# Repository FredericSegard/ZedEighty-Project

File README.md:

# ZedEighty Project
 My Z80 adventures

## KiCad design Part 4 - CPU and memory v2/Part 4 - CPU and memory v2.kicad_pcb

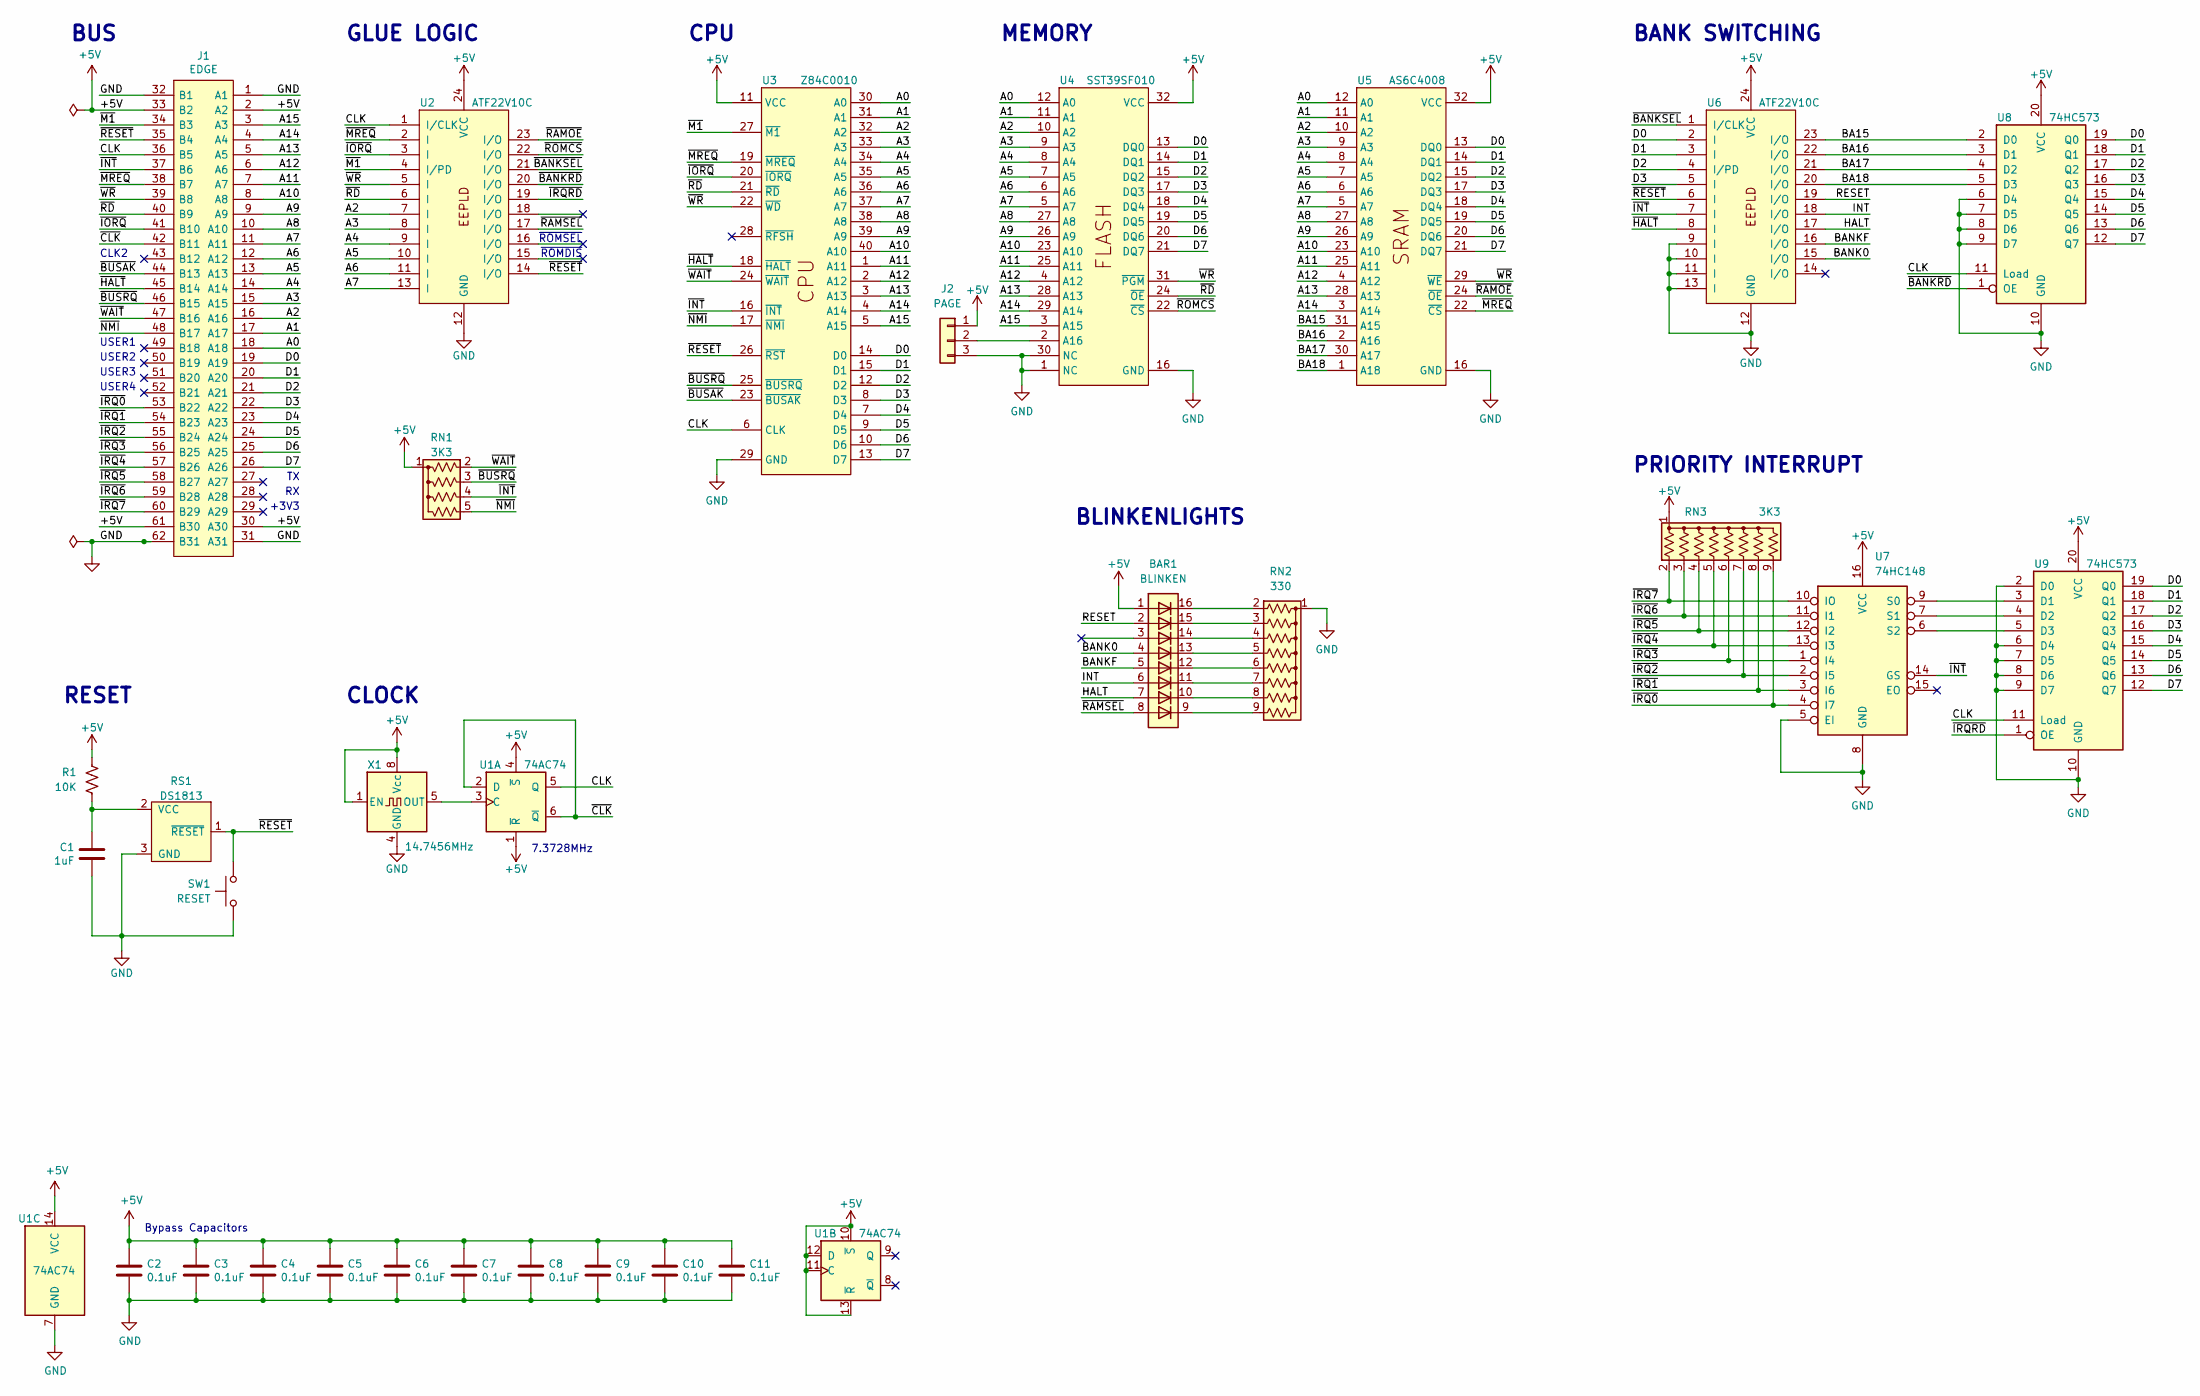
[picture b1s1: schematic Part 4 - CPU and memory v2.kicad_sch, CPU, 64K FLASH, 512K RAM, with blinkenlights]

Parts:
BAR1: BLINKEN; 8_Segment_Bar_graph
C1: 1uF; C_Disc_D3.0mm_W2.0mm_P2.50mm
C2, C3, C4, C5, C6, C7, C8, C9, C10, C11: 0.1uF; C_Disc_D3.0mm_W1.6mm_P2.50mm
J1: EDGE; BUS_XT; Mouser Part Number 571-6-5530843-5
J2: PAGE; PinHeader_1x03_P2.54mm_Vertical
R1: 10K; R_Axial_DIN0207_L6.3mm_D2.5mm_P10.16mm_Horizontal
RN1: 3K3; R_Array_SIP5
RN2: 330; R_Array_SIP9
RN3: 3K3; R_Array_SIP9
RS1: DS1813; TO-92L_Inline_Wide
SW1: RESET; SW_Tactile_SPST_Angled_PTS645Vx58-2LFS
U1: 74AC74; DIP-14_W7.62mm_Socket
U2, U6: ATF22V10C; DIP-24_W7.62mm_Socket
U3: Z84C0010; DIP-40_W15.24mm_Socket
U4: SST39SF010; DIP_Socket-32_W11.9_W12.7_W15.24_W17.78_W18.5_3M_232-1285-0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
U5: AS6C4008; DIP-32_W15.24mm_Socket
U7: 74HC148; DIP-16_W7.62mm_Socket
U8, U9: 74HC573; DIP-20_W7.62mm_Socket
X1: 14.7456MHz; DIP-8-4_W7.62mm_Oscillator_Socket

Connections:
+5V: BAR1.1 (A), C2.1, C3.1, C4.1, C5.1, C6.1, C7.1, C8.1, C9.1, C10.1, C11.1, J1.2 (A2), J1.30 (A30), J1.33 (B2), J1.61 (B30), J2.1, R1.2, RN1.1 (common), RN3.1 (common), U1.1 (~R), U1.4 (~S), U1.10 (~S), U1.11 (C), U1.12 (D), U1.13 (~R), U1.14 (VCC), U2.24 (VCC), U3.11 (VCC), U4.32 (VCC), U5.32 (VCC), U6.24 (VCC), U7.16 (VCC), U8.20 (VCC), U9.20 (VCC), X1.1 (EN), X1.8 (Vcc)
/A0: J1.18 (A18), U3.30 (A0), U4.12 (A0), U5.12 (A0)
/A1: J1.17 (A17), U3.31 (A1), U4.11 (A1), U5.11 (A1)
/A2: J1.16 (A16), U2.7 (I), U3.32 (A2), U4.10 (A2), U5.10 (A2)
/A3: J1.15 (A15), U2.8 (I), U3.33 (A3), U4.9 (A3), U5.9 (A3)
/A4: J1.14 (A14), U2.9 (I), U3.34 (A4), U4.8 (A4), U5.8 (A4)
/A5: J1.13 (A13), U2.10 (I), U3.35 (A5), U4.7 (A5), U5.7 (A5)
/A6: J1.12 (A12), U2.11 (I), U3.36 (A6), U4.6 (A6), U5.6 (A6)
/A7: J1.11 (A11), U2.13 (I), U3.37 (A7), U4.5 (A7), U5.5 (A7)
/A8: J1.10 (A10), U3.38 (A8), U4.27 (A8), U5.27 (A8)
/A9: J1.9 (A9), U3.39 (A9), U4.26 (A9), U5.26 (A9)
/A10: J1.8 (A8), U3.40 (A10), U4.23 (A10), U5.23 (A10)
/A11: J1.7 (A7), U3.1 (A11), U4.25 (A11), U5.25 (A11)
/A12: J1.6 (A6), U3.2 (A12), U4.4 (A12), U5.4 (A12)
/A13: J1.5 (A5), U3.3 (A13), U4.28 (A13), U5.28 (A13)
/A14: J1.4 (A4), U3.4 (A14), U4.29 (A14), U5.3 (A14)
/A15: J1.3 (A3), U3.5 (A15), U4.3 (A15)
/BA15: U5.31 (A15), U6.23 (I/O), U8.2 (D0)
/BA16: U5.2 (A16), U6.22 (I/O), U8.3 (D1)
/BA17: U5.30 (A17), U6.21 (I/O), U8.4 (D2)
/BA18: U5.1 (A18), U6.20 (I/O), U8.5 (D3)
/BANK0: BAR1.4 (A), U6.15 (I/O)
/BANKF: BAR1.5 (A), U6.16 (I/O)
/CLK: J1.36 (B5), U1.5 (Q), U2.1 (I/CLK), U3.6 (CLK), U8.11 (Load), U9.11 (Load)
/D0: J1.19 (A19), U3.14 (D0), U4.13 (DQ0), U5.13 (DQ0), U6.2 (I), U8.19 (Q0), U9.19 (Q0)
/D1: J1.20 (A20), U3.15 (D1), U4.14 (DQ1), U5.14 (DQ1), U6.3 (I), U8.18 (Q1), U9.18 (Q1)
/D2: J1.21 (A21), U3.12 (D2), U4.15 (DQ2), U5.15 (DQ2), U6.4 (I/PD), U8.17 (Q2), U9.17 (Q2)
/D3: J1.22 (A22), U3.8 (D3), U4.17 (DQ3), U5.17 (DQ3), U6.5 (I), U8.16 (Q3), U9.16 (Q3)
/D4: J1.23 (A23), U3.7 (D4), U4.18 (DQ4), U5.18 (DQ4), U8.15 (Q4), U9.15 (Q4)
/D5: J1.24 (A24), U3.9 (D5), U4.19 (DQ5), U5.19 (DQ5), U8.14 (Q5), U9.14 (Q5)
/D6: J1.25 (A25), U3.10 (D6), U4.20 (DQ6), U5.20 (DQ6), U8.13 (Q6), U9.13 (Q6)
/D7: J1.26 (A26), U3.13 (D7), U4.21 (DQ7), U5.21 (DQ7), U8.12 (Q7), U9.12 (Q7)
/HALT: BAR1.7 (A), U6.17 (I/O)
/INT: BAR1.6 (A), U6.18 (I/O)
/RESET: BAR1.2 (A), U6.19 (I/O)
/~BANKRD: U2.20 (I/O), U8.1 (OE)
/~BANKSEL: U2.21 (I/O), U6.1 (I/CLK)
/~BUSAK: J1.44 (B13), U3.23 (~BUSAK)
/~BUSRQ: J1.46 (B15), RN1.3 (R2), U3.25 (~BUSRQ)
/~CLK: J1.42 (B11), U1.2 (D), U1.6 (~Q)
/~HALT: J1.45 (B14), U3.18 (~HALT), U6.8 (I)
/~INT: J1.37 (B6), RN1.4 (R3), U3.16 (~INT), U6.7 (I), U7.14 (GS)
/~IORQ: J1.41 (B10), U2.3 (I), U3.20 (~IORQ)
/~IRQ0: J1.53 (B22), RN3.9 (R8), U7.4 (I7)
/~IRQ1: J1.54 (B23), RN3.8 (R7), U7.3 (I6)
/~IRQ2: J1.55 (B24), RN3.7 (R6), U7.2 (I5)
/~IRQ3: J1.56 (B25), RN3.6 (R5), U7.1 (I4)
/~IRQ4: J1.57 (B26), RN3.5 (R4), U7.13 (I3)
/~IRQ5: J1.58 (B27), RN3.4 (R3), U7.12 (I2)
/~IRQ6: J1.59 (B28), RN3.3 (R2), U7.11 (I1)
/~IRQ7: J1.60 (B29), RN3.2 (R1), U7.10 (IO)
/~IRQRD: U2.19 (I/O), U9.1 (OE)
/~M1: J1.34 (B3), U2.4 (I/PD), U3.27 (~M1)
/~MREQ: J1.38 (B7), U2.2 (I), U3.19 (~MREQ), U5.22 (~CS)
/~NMI: J1.48 (B17), RN1.5 (R4), U3.17 (~NMI)
/~RAMOE: U2.23 (I/O), U5.24 (~OE)
/~RAMSEL: BAR1.8 (A), U2.17 (I/O)
/~RD: J1.40 (B9), U2.6 (I), U3.21 (~RD), U4.24 (~OE)
/~RESET: J1.35 (B4), RS1.1 (~RESET), SW1.1, U2.14 (I/O), U3.26 (~RST), U6.6 (I)
/~ROMCS: U2.22 (I/O), U4.22 (~CS)
/~WAIT: J1.47 (B16), RN1.2 (R1), U3.24 (~WAIT)
/~WR: J1.39 (B8), U2.5 (I), U3.22 (~WD), U4.31 (~PGM), U5.29 (~WE)
GND: C1.2, C2.2, C3.2, C4.2, C5.2, C6.2, C7.2, C8.2, C9.2, C10.2, C11.2, J1.1 (A1), J1.31 (A31), J1.32 (B1), J1.62 (B31), J2.3, RN2.1 (common), RS1.3 (GND), SW1.2, U1.7 (GND), U2.12 (GND), U3.29 (GND), U4.1 (NC), U4.16 (GND), U4.30 (NC), U5.16 (GND), U6.9 (I), U6.10 (I), U6.11 (I), U6.12 (GND), U6.13 (I), U7.5 (EI), U7.8 (GND), U8.6 (D4), U8.7 (D5), U8.8 (D6), U8.9 (D7), U8.10 (GND), U9.2 (D0), U9.6 (D4), U9.7 (D5), U9.8 (D6), U9.9 (D7), U9.10 (GND), X1.4 (GND)
unnamed: BAR1.9 (A), RN2.9 (R8)
unnamed: BAR1.10 (A), RN2.8 (R7)
unnamed: BAR1.11 (K), RN2.7 (R6)
unnamed: BAR1.12 (K), RN2.6 (R5)
unnamed: BAR1.13 (K), RN2.5 (R4)
unnamed: BAR1.14 (K), RN2.4 (R3)
unnamed: BAR1.15 (K), RN2.3 (R2)
unnamed: BAR1.16 (K), RN2.2 (R1)
unnamed: C1.1, R1.1, RS1.2 (VCC)
unnamed: J2.2, U4.2 (A16)
unnamed: U1.3 (C), X1.5 (OUT)
unnamed: U7.6 (S2), U9.5 (D3)
unnamed: U7.7 (S1), U9.4 (D2)
unnamed: U7.9 (S0), U9.3 (D1)

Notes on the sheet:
MEMORY
BUS
BLINKENLIGHTS
CLK2
CPU
PRIORITY INTERRUPT
USER2
RESET
USER4
7.3728MHz
BANK SWITCHING
USER3
USER1
~{ROMDIS}
Bypass Capacitors
CLOCK
GLUE LOGIC
+3V3
~{ROMSEL}

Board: 2 copper layers, 30 parts (0 on the bottom side), 77 nets, no tracks yet.

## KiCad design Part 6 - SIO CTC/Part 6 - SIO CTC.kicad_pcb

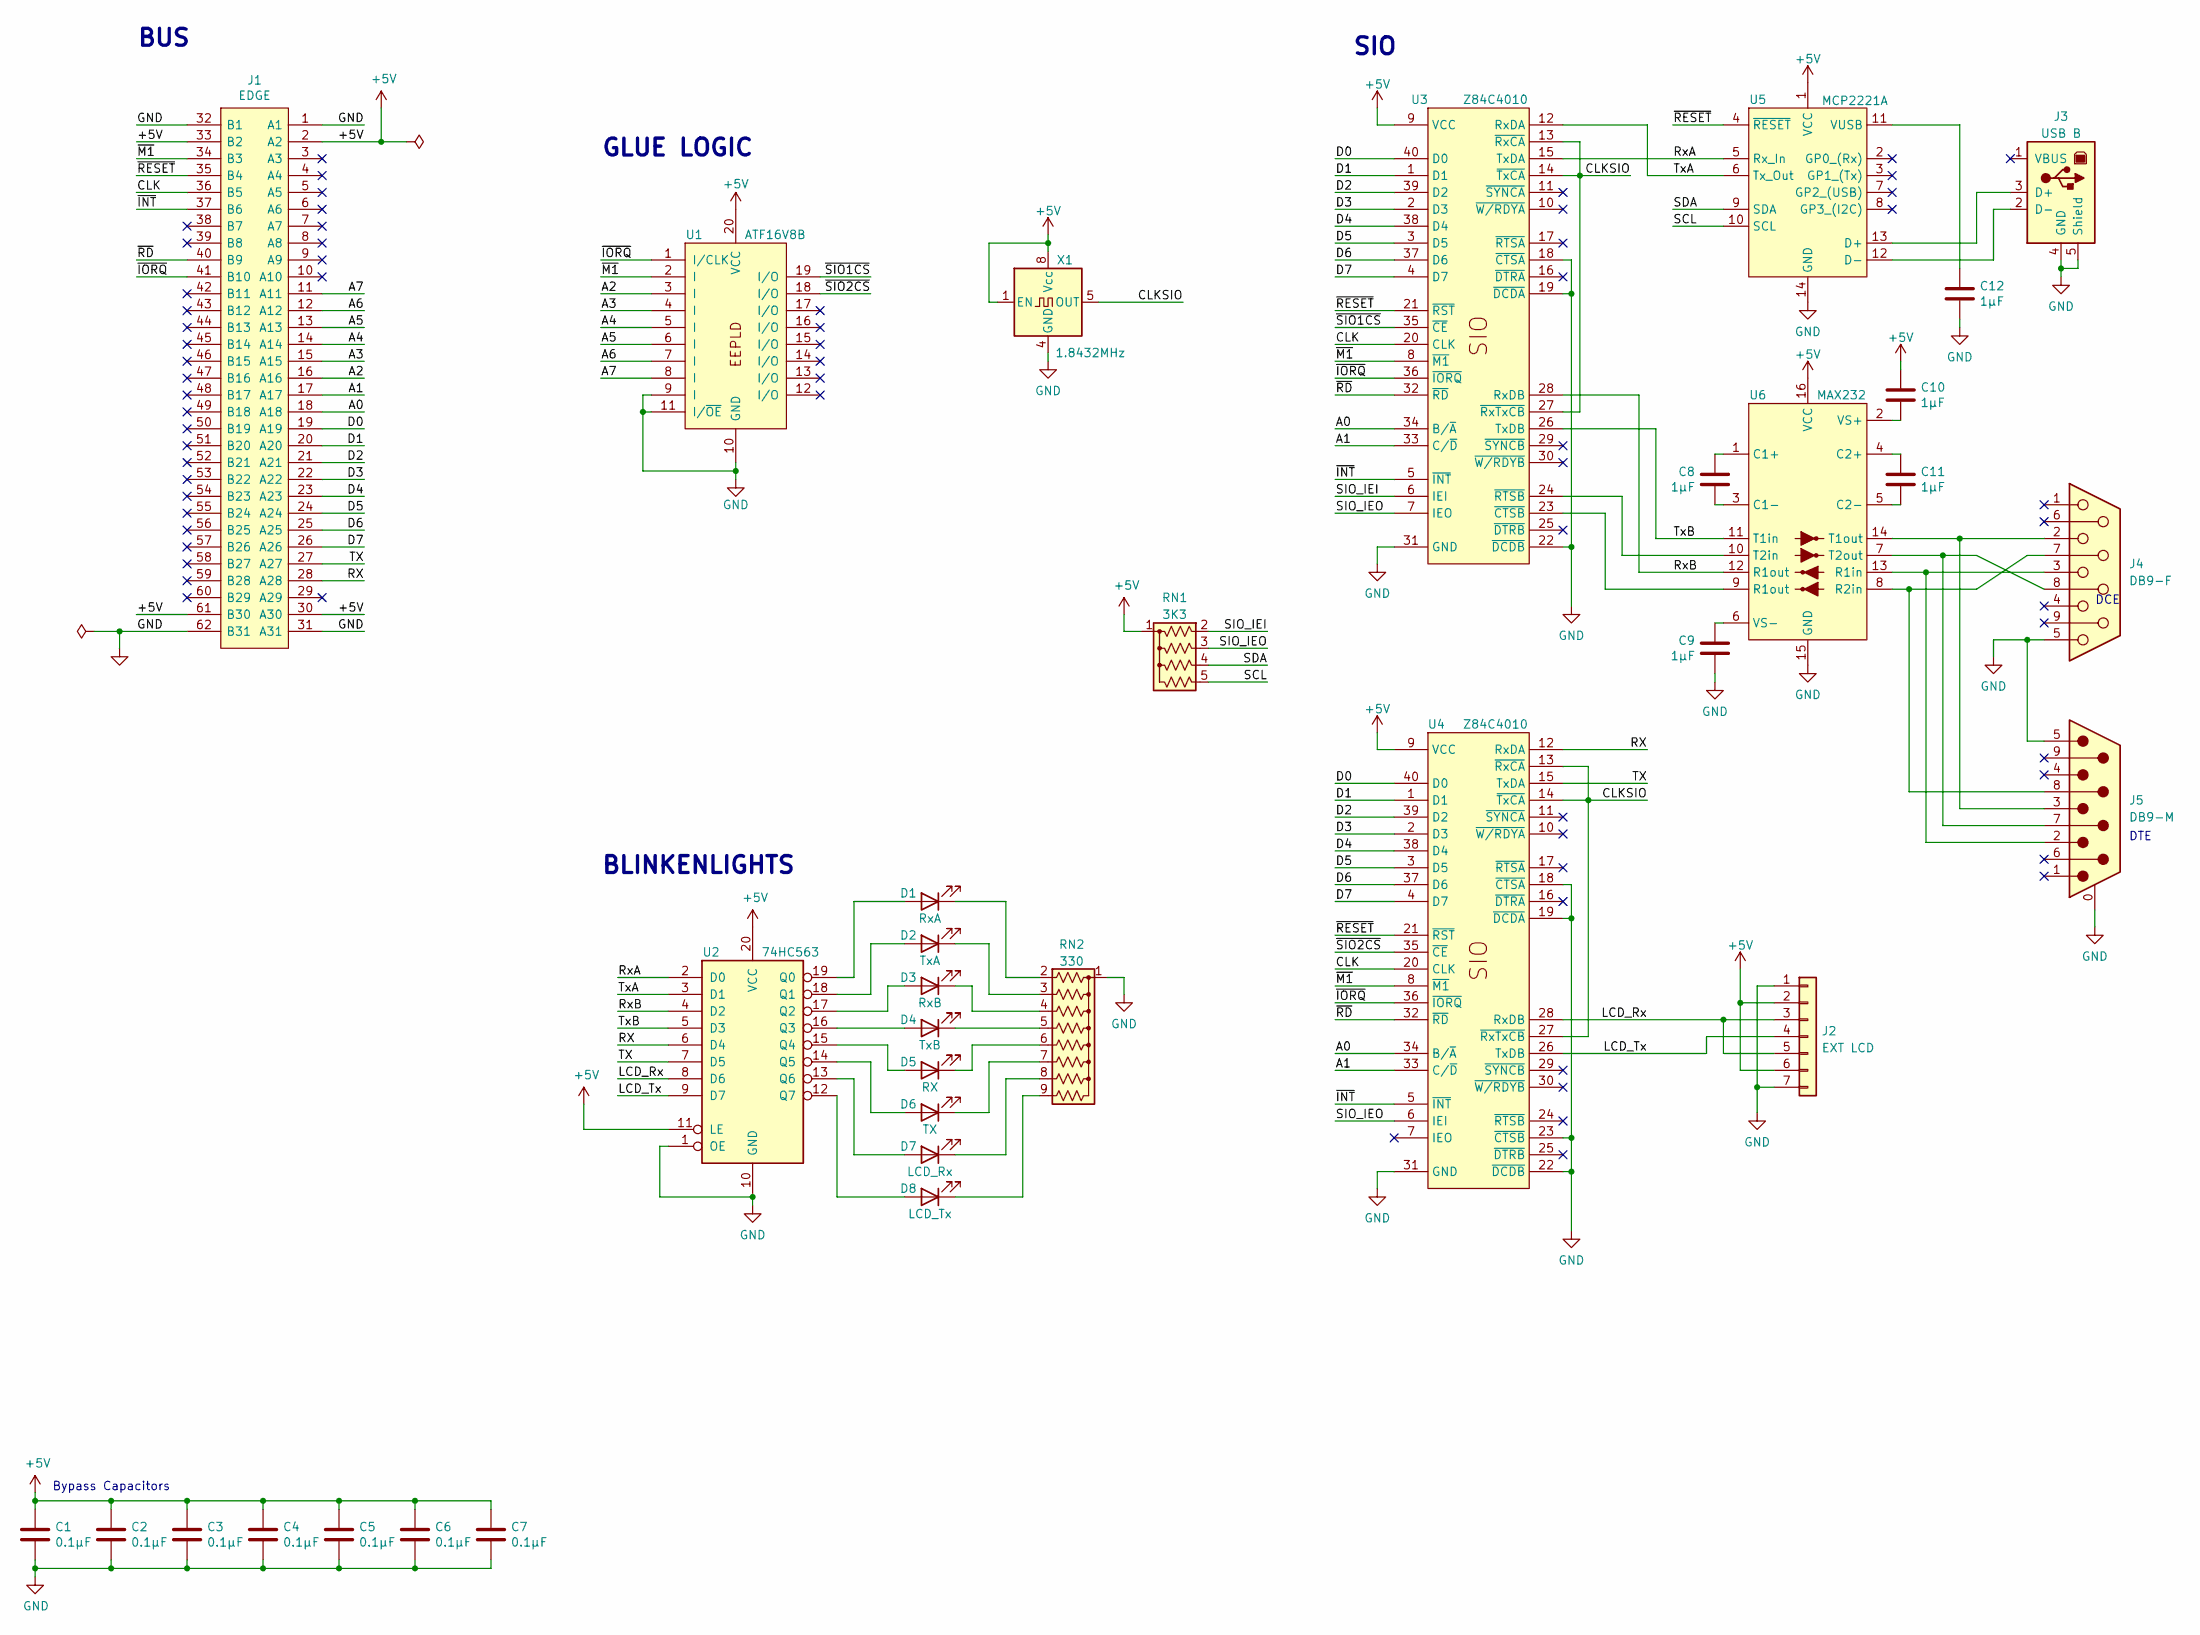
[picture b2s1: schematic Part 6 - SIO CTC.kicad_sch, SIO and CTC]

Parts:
C1, C2, C3, C4, C5, C6, C7: 0.1µF; C_Disc_D3.0mm_W1.6mm_P2.50mm
C8, C9, C10, C11, C12: 1µF; C_Disc_D3.0mm_W1.6mm_P2.50mm
D1: RxA; LED_D3.0mm_Horizontal_O1.27mm_Z2.0mm_Clear
D2: TxA; LED_D3.0mm_Horizontal_O1.27mm_Z2.0mm_Clear
D3: RxB; LED_D3.0mm_Horizontal_O1.27mm_Z2.0mm_Clear
D4: TxB; LED_D3.0mm_Horizontal_O1.27mm_Z2.0mm_Clear
D5: RX; LED_D3.0mm_Horizontal_O1.27mm_Z2.0mm_Clear
D6: TX; LED_D3.0mm_Horizontal_O1.27mm_Z2.0mm_Clear
D7: LCD_Rx; LED_D3.0mm_Horizontal_O1.27mm_Z2.0mm_Clear
D8: LCD_Tx; LED_D3.0mm_Horizontal_O1.27mm_Z2.0mm_Clear
J1: EDGE; BUS_XT; Mouser Part Number 571-6-5530843-5
J2: EXT LCD; PinHeader_1x07_P2.54mm_Horizontal
J3: USB B; USB_B_Lumberg_2411_02_Horizontal
J4: DB9-F; DSUB-9_Female_Horizontal_P2.77x2.84mm_EdgePinOffset7.70mm_H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
J5: DB9-M; DSUB-9_Male_Horizontal_P2.77x2.84mm_EdgePinOffset7.70mm_Hou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
RN1: 3K3; R_Array_SIP5
RN2: 330; R_Array_SIP9
U1: ATF16V8B; DIP-20_W7.62mm_Socket
U2: 74HC563; DIP-20_W7.62mm_Socket
U3, U4: Z84C4010; DIP-40_W15.24mm_Socket
U5: MCP2221A; DIP-14_W7.62mm_Socket
U6: MAX232; DIP-16_W7.62mm_Socket
X1: 1.8432MHz; DIP-8-4_W7.62mm_Oscillator_Socket

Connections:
+5V: C1.1, C2.1, C3.1, C4.1, C5.1, C6.1, C7.1, C10.1, J1.2 (A2), J1.30 (A30), J1.33 (B2), J1.61 (B30), J2.2, J2.6, RN1.1 (common), U1.20 (VCC), U2.11 (LE), U2.20 (VCC), U3.9 (VCC), U4.9 (VCC), U5.1 (VCC), U6.16 (VCC), X1.1 (EN), X1.8 (Vcc)
/A0: J1.18 (A18), U3.34 (B/~A), U4.34 (B/~A)
/A1: J1.17 (A17), U3.33 (C/~D), U4.33 (C/~D)
/A2: J1.16 (A16), U1.3 (I)
/A3: J1.15 (A15), U1.4 (I)
/A4: J1.14 (A14), U1.5 (I)
/A5: J1.13 (A13), U1.6 (I)
/A6: J1.12 (A12), U1.7 (I)
/A7: J1.11 (A11), U1.8 (I)
/CLK: J1.36 (B5), U3.20 (CLK), U4.20 (CLK)
/CLKSIO: U3.13 (~RxCA), U3.14 (~TxCA), U3.27 (~RxTxCB), U4.13 (~RxCA), U4.14 (~TxCA), U4.27 (~RxTxCB), X1.5 (OUT)
/D0: J1.19 (A19), U3.40 (D0), U4.40 (D0)
/D1: J1.20 (A20), U3.1 (D1), U4.1 (D1)
/D2: J1.21 (A21), U3.39 (D2), U4.39 (D2)
/D3: J1.22 (A22), U3.2 (D3), U4.2 (D3)
/D4: J1.23 (A23), U3.38 (D4), U4.38 (D4)
/D5: J1.24 (A24), U3.3 (D5), U4.3 (D5)
/D6: J1.25 (A25), U3.37 (D6), U4.37 (D6)
/D7: J1.26 (A26), U3.4 (D7), U4.4 (D7)
/LCD_Rx: J2.3, J2.5, U2.8 (D6), U4.28 (RxDB)
/LCD_Tx: J2.4, U2.9 (D7), U4.26 (TxDB)
/RX: J1.28 (A28), U2.6 (D4), U4.12 (RxDA)
/RxA: U2.2 (D0), U3.15 (TxDA), U5.5 (Rx_In)
/RxB: U2.4 (D2), U3.28 (RxDB), U6.12 (R1out)
/SCL: RN1.5 (R4), U5.10 (SCL)
/SDA: RN1.4 (R3), U5.9 (SDA)
/SIO_IEI: RN1.2 (R1), U3.6 (IEI)
/SIO_IEO: RN1.3 (R2), U3.7 (IEO), U4.6 (IEI)
/TX: J1.27 (A27), U2.7 (D5), U4.15 (TxDA)
/TxA: U2.3 (D1), U3.12 (RxDA), U5.6 (Tx_Out)
/TxB: U2.5 (D3), U3.26 (TxDB), U6.11 (T1in)
/~INT: J1.37 (B6), U3.5 (~INT), U4.5 (~INT)
/~IORQ: J1.41 (B10), U1.1 (I/CLK), U3.36 (~IORQ), U4.36 (~IORQ)
/~M1: J1.34 (B3), U1.2 (I), U3.8 (~M1), U4.8 (~M1)
/~RD: J1.40 (B9), U3.32 (~RD), U4.32 (~RD)
/~RESET: J1.35 (B4), U3.21 (~RST), U4.21 (~RST), U5.4 (~RESET)
/~SIO1CS: U1.19 (I/O), U3.35 (~CE)
/~SIO2CS: U1.18 (I/O), U4.35 (~CE)
GND: C1.2, C2.2, C3.2, C4.2, C5.2, C6.2, C7.2, C9.2, C12.2, J1.1 (A1), J1.31 (A31), J1.32 (B1), J1.62 (B31), J2.1, J2.7, J3.4 (GND), J3.5 (Shield), J4.5, J5.0 (PAD), J5.5, RN2.1 (common), U1.9 (I), U1.10 (GND), U1.11 (I/~OE), U2.1 (OE), U2.10 (GND), U3.18 (~CTSA), U3.19 (~DCDA), U3.22 (~DCDB), U3.31 (GND), U4.18 (~CTSA), U4.19 (~DCDA), U4.22 (~DCDB), U4.23 (~CTSB), U4.31 (GND), U5.14 (GND), U6.15 (GND), X1.4 (GND)
unnamed: C8.1, U6.1 (C1+)
unnamed: C8.2, U6.3 (C1-)
unnamed: C9.1, U6.6 (VS-)
unnamed: C10.2, U6.2 (VS+)
unnamed: C11.1, U6.4 (C2+)
unnamed: C11.2, U6.5 (C2-)
unnamed: C12.1, U5.11 (VUSB)
unnamed: D1.1 (K), RN2.2 (R1)
unnamed: D1.2 (A), U2.19 (Q0)
unnamed: D2.1 (K), RN2.3 (R2)
unnamed: D2.2 (A), U2.18 (Q1)
unnamed: D3.1 (K), RN2.4 (R3)
unnamed: D3.2 (A), U2.17 (Q2)
unnamed: D4.1 (K), RN2.5 (R4)
unnamed: D4.2 (A), U2.16 (Q3)
unnamed: D5.1 (K), RN2.6 (R5)
unnamed: D5.2 (A), U2.15 (Q4)
unnamed: D6.1 (K), RN2.7 (R6)
unnamed: D6.2 (A), U2.14 (Q5)
unnamed: D7.1 (K), RN2.8 (R7)
unnamed: D7.2 (A), U2.13 (Q6)
unnamed: D8.1 (K), RN2.9 (R8)
unnamed: D8.2 (A), U2.12 (Q7)
unnamed: J3.2 (D-), U5.12 (D-)
unnamed: J3.3 (D+), U5.13 (D+)
unnamed: J4.2, J5.3, U6.14 (T1out)
unnamed: J4.3, J5.2, U6.13 (R1in)
unnamed: J4.7, J5.8, U6.8 (R2in)
unnamed: J4.8, J5.7, U6.7 (T2out)
unnamed: U3.23 (~CTSB), U6.9 (R1out)
unnamed: U3.24 (~RTSB), U6.10 (T2in)

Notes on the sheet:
DTE
BLINKENLIGHTS
BUS
SIO
Bypass Capacitors
GLUE LOGIC
DCE

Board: 2 copper layers, 34 parts (0 on the bottom side), 70 nets, no tracks yet.

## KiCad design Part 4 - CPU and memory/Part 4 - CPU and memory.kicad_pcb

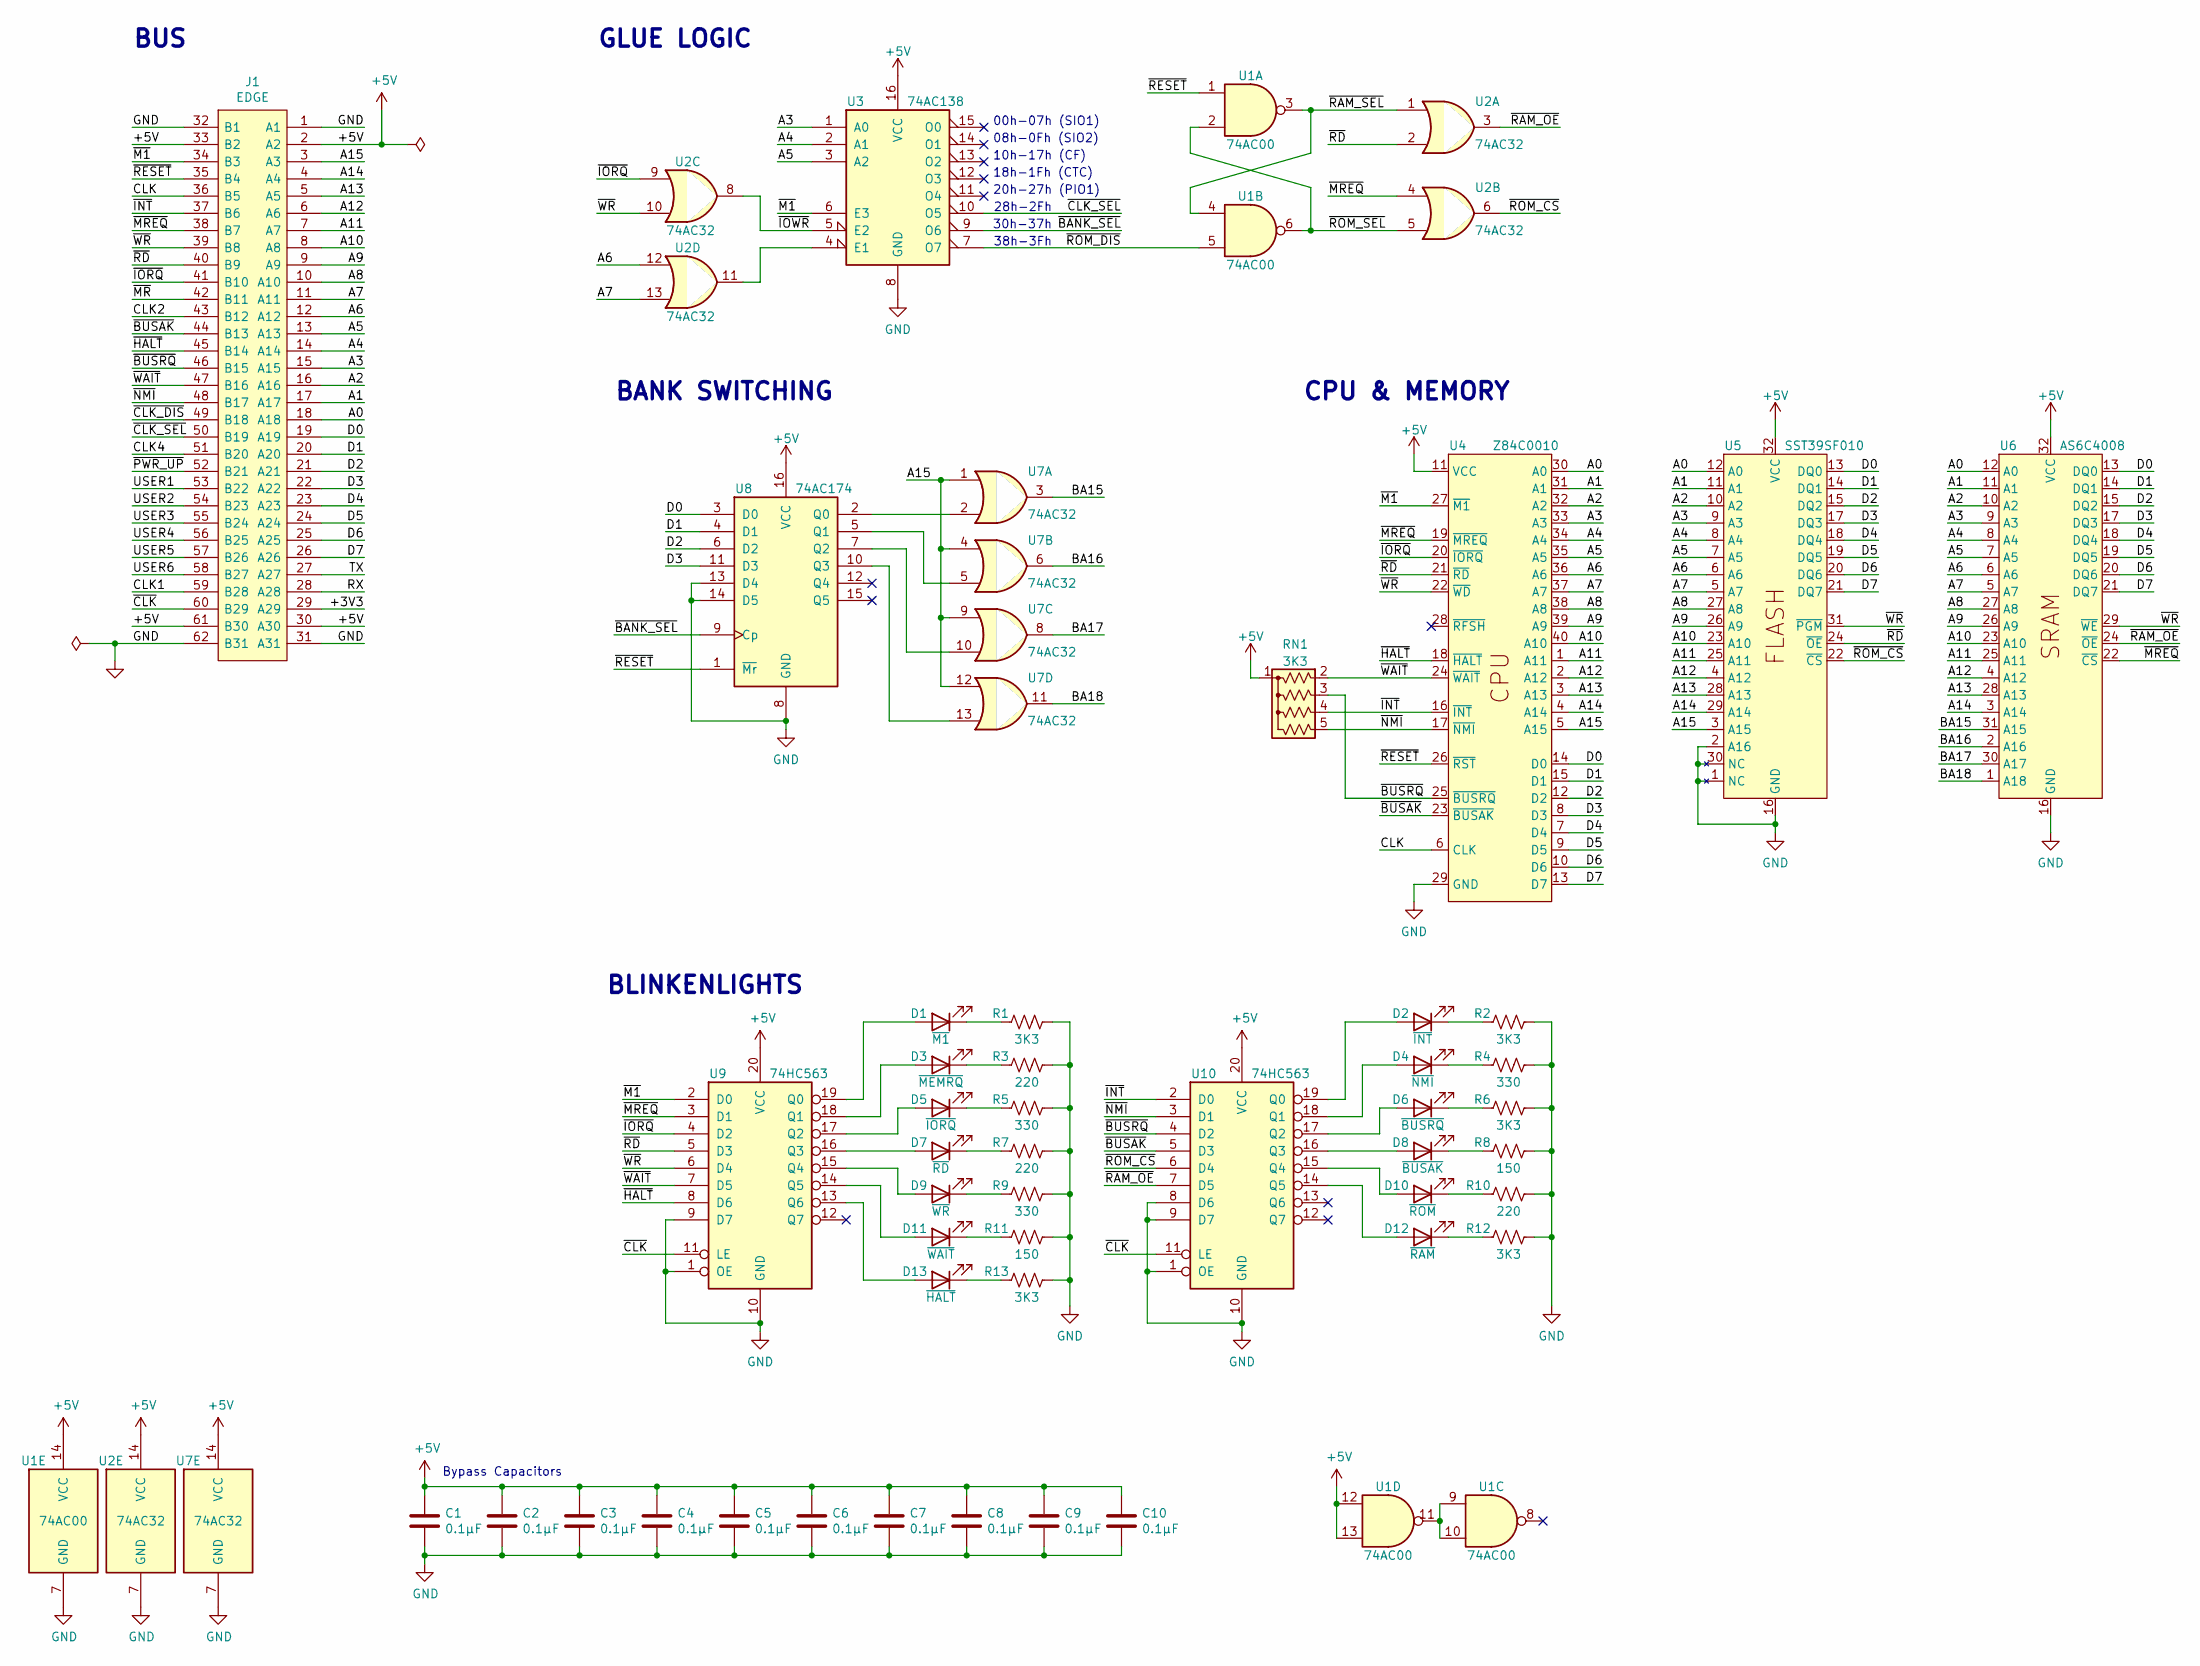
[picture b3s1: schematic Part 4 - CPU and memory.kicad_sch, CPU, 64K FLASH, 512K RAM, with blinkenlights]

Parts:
C1, C2, C3, C4, C5, C6, C7, C8, C9, C10: 0.1µF; C_Disc_D3.0mm_W1.6mm_P2.50mm
D1: ~{M1}; LED_D3.0mm_Horizontal_O1.27mm_Z2.0mm_Clear
D2: ~{INT}; LED_D3.0mm_Horizontal_O1.27mm_Z2.0mm_Clear
D3: ~{MEMRQ}; LED_D3.0mm_Horizontal_O1.27mm_Z2.0mm_Clear
D4: ~{NMI}; LED_D3.0mm_Horizontal_O1.27mm_Z2.0mm_Clear
D5: ~{IORQ}; LED_D3.0mm_Horizontal_O1.27mm_Z2.0mm_Clear
D6: ~{BUSRQ}; LED_D3.0mm_Horizontal_O1.27mm_Z2.0mm_Clear
D7: ~{RD}; LED_D3.0mm_Horizontal_O1.27mm_Z2.0mm_Clear
D8: ~{BUSAK}; LED_D3.0mm_Horizontal_O1.27mm_Z2.0mm_Clear
D9: ~{WR}; LED_D3.0mm_Horizontal_O1.27mm_Z2.0mm_Clear
D10: ~{ROM}; LED_D3.0mm_Horizontal_O1.27mm_Z2.0mm_Clear
D11: ~{WAIT}; LED_D3.0mm_Horizontal_O1.27mm_Z2.0mm_Clear
D12: ~{RAM}; LED_D3.0mm_Horizontal_O1.27mm_Z2.0mm_Clear
D13: ~{HALT}; LED_D3.0mm_Horizontal_O1.27mm_Z2.0mm_Clear
J1: EDGE; BUS_XT; Mouser Part Number 571-6-5530843-5
R1, R2, R6, R12, R13: 3K3; R_Axial_DIN0207_L6.3mm_D2.5mm_P10.16mm_Horizontal
R3, R7, R10: 220; R_Axial_DIN0207_L6.3mm_D2.5mm_P10.16mm_Horizontal
R4, R5, R9: 330; R_Axial_DIN0207_L6.3mm_D2.5mm_P10.16mm_Horizontal
R8, R11: 150; R_Axial_DIN0207_L6.3mm_D2.5mm_P10.16mm_Horizontal
RN1: 3K3; R_Array_SIP5
U1: 74AC00; DIP-14_W7.62mm_Socket
U2, U7: 74AC32; DIP-14_W7.62mm_Socket
U3: 74AC138; DIP-16_W7.62mm_Socket
U4: Z84C0010; DIP-40_W15.24mm_Socket
U5: SST39SF010; DIP-32_W15.24mm_Socket
U6: AS6C4008; DIP-32_W15.24mm_Socket
U8: 74AC174; DIP-16_W7.62mm_Socket
U9, U10: 74HC563; DIP-20_W7.62mm_Socket

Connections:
+5V: C1.1, C2.1, C3.1, C4.1, C5.1, C6.1, C7.1, C8.1, C9.1, C10.1, J1.2 (A2), J1.30 (A30), J1.33 (B2), J1.61 (B30), RN1.1 (common), U1.12, U1.13, U1.14 (VCC), U2.14 (VCC), U3.16 (VCC), U4.11 (VCC), U5.32 (VCC), U6.32 (VCC), U7.14 (VCC), U8.16 (VCC), U9.20 (VCC), U10.20 (VCC)
/+3V3: J1.29 (A29)
/A0: J1.18 (A18), U4.30 (A0), U5.12 (A0), U6.12 (A0)
/A1: J1.17 (A17), U4.31 (A1), U5.11 (A1), U6.11 (A1)
/A2: J1.16 (A16), U4.32 (A2), U5.10 (A2), U6.10 (A2)
/A3: J1.15 (A15), U3.1 (A0), U4.33 (A3), U5.9 (A3), U6.9 (A3)
/A4: J1.14 (A14), U3.2 (A1), U4.34 (A4), U5.8 (A4), U6.8 (A4)
/A5: J1.13 (A13), U3.3 (A2), U4.35 (A5), U5.7 (A5), U6.7 (A5)
/A6: J1.12 (A12), U2.12, U4.36 (A6), U5.6 (A6), U6.6 (A6)
/A7: J1.11 (A11), U2.13, U4.37 (A7), U5.5 (A7), U6.5 (A7)
/A8: J1.10 (A10), U4.38 (A8), U5.27 (A8), U6.27 (A8)
/A9: J1.9 (A9), U4.39 (A9), U5.26 (A9), U6.26 (A9)
/A10: J1.8 (A8), U4.40 (A10), U5.23 (A10), U6.23 (A10)
/A11: J1.7 (A7), U4.1 (A11), U5.25 (A11), U6.25 (A11)
/A12: J1.6 (A6), U4.2 (A12), U5.4 (A12), U6.4 (A12)
/A13: J1.5 (A5), U4.3 (A13), U5.28 (A13), U6.28 (A13)
/A14: J1.4 (A4), U4.4 (A14), U5.29 (A14), U6.3 (A14)
/A15: J1.3 (A3), U4.5 (A15), U5.3 (A15), U7.1, U7.4, U7.9, U7.12
/BA15: U6.31 (A15), U7.3
/BA16: U6.2 (A16), U7.6
/BA17: U6.30 (A17), U7.8
/BA18: U6.1 (A18), U7.11
/CLK: J1.36 (B5), U4.6 (CLK)
/CLK1: J1.59 (B28)
/CLK2: J1.43 (B12)
/CLK4: J1.51 (B20)
/D0: J1.19 (A19), U4.14 (D0), U5.13 (DQ0), U6.13 (DQ0), U8.3 (D0)
/D1: J1.20 (A20), U4.15 (D1), U5.14 (DQ1), U6.14 (DQ1), U8.4 (D1)
/D2: J1.21 (A21), U4.12 (D2), U5.15 (DQ2), U6.15 (DQ2), U8.6 (D2)
/D3: J1.22 (A22), U4.8 (D3), U5.17 (DQ3), U6.17 (DQ3), U8.11 (D3)
/D4: J1.23 (A23), U4.7 (D4), U5.18 (DQ4), U6.18 (DQ4)
/D5: J1.24 (A24), U4.9 (D5), U5.19 (DQ5), U6.19 (DQ5)
/D6: J1.25 (A25), U4.10 (D6), U5.20 (DQ6), U6.20 (DQ6)
/D7: J1.26 (A26), U4.13 (D7), U5.21 (DQ7), U6.21 (DQ7)
/RX: J1.28 (A28)
/TX: J1.27 (A27)
/USER1: J1.53 (B22)
/USER2: J1.54 (B23)
/USER3: J1.55 (B24)
/USER4: J1.56 (B25)
/USER5: J1.57 (B26)
/USER6: J1.58 (B27)
/~BANK_SEL: U3.9 (O6), U8.9 (Cp)
/~BUSAK: J1.44 (B13), U4.23 (~BUSAK), U10.5 (D3)
/~BUSRQ: J1.46 (B15), RN1.3 (R2), U4.25 (~BUSRQ), U10.4 (D2)
/~CLK_DIS: J1.49 (B18)
/~CLK_SEL: J1.50 (B19), U3.10 (O5)
/~CLK: J1.60 (B29), U9.11 (LE), U10.11 (LE)
/~HALT: J1.45 (B14), U4.18 (~HALT), U9.8 (D6)
/~INT: J1.37 (B6), RN1.4 (R3), U4.16 (~INT), U10.2 (D0)
/~IORQ: J1.41 (B10), U2.9, U4.20 (~IORQ), U9.4 (D2)
/~IOWR: U2.8, U3.5 (E2)
/~M1: J1.34 (B3), U3.6 (E3), U4.27 (~M1), U9.2 (D0)
/~MREQ: J1.38 (B7), U2.4, U4.19 (~MREQ), U6.22 (~CS), U9.3 (D1)
/~MR: J1.42 (B11)
/~NMI: J1.48 (B17), RN1.5 (R4), U4.17 (~NMI), U10.3 (D1)
/~PWR_UP: J1.52 (B21)
/~RAM_OE: U2.3, U6.24 (~OE), U10.7 (D5)
/~RAM_SEL: U1.3, U1.4, U2.1
/~RD: J1.40 (B9), U2.2, U4.21 (~RD), U5.24 (~OE), U9.5 (D3)
/~RESET: J1.35 (B4), U1.1, U4.26 (~RST), U8.1 (~Mr)
/~ROM_CS: U2.6, U5.22 (~CS), U10.6 (D4)
/~ROM_DIS: U1.5, U3.7 (O7)
/~ROM_SEL: U1.2, U1.6, U2.5
/~WAIT: J1.47 (B16), RN1.2 (R1), U4.24 (~WAIT), U9.7 (D5)
/~WR: J1.39 (B8), U2.10, U4.22 (~WD), U5.31 (~PGM), U6.29 (~WE), U9.6 (D4)
GND: C1.2, C2.2, C3.2, C4.2, C5.2, C6.2, C7.2, C8.2, C9.2, C10.2, J1.1 (A1), J1.31 (A31), J1.32 (B1), J1.62 (B31), R1.2, R2.2, R3.2, R4.2, R5.2, R6.2, R7.2, R8.2, R9.2, R10.2, R11.2, R12.2, R13.2, U1.7 (GND), U2.7 (GND), U3.8 (GND), U4.29 (GND), U5.1 (NC), U5.2 (A16), U5.16 (GND), U5.30 (NC), U6.16 (GND), U7.7 (GND), U8.8 (GND), U8.13 (D4), U8.14 (D5), U9.1 (OE), U9.9 (D7), U9.10 (GND), U10.1 (OE), U10.8 (D6), U10.9 (D7), U10.10 (GND)
unnamed: D1.1 (K), R1.1
unnamed: D1.2 (A), U9.19 (Q0)
unnamed: D2.1 (K), R2.1
unnamed: D2.2 (A), U10.19 (Q0)
unnamed: D3.1 (K), R3.1
unnamed: D3.2 (A), U9.18 (Q1)
unnamed: D4.1 (K), R4.1
unnamed: D4.2 (A), U10.18 (Q1)
unnamed: D5.1 (K), R5.1
unnamed: D5.2 (A), U9.17 (Q2)
unnamed: D6.1 (K), R6.1
unnamed: D6.2 (A), U10.17 (Q2)
unnamed: D7.1 (K), R7.1
unnamed: D7.2 (A), U9.16 (Q3)
unnamed: D8.1 (K), R8.1
unnamed: D8.2 (A), U10.16 (Q3)
unnamed: D9.1 (K), R9.1
unnamed: D9.2 (A), U9.15 (Q4)
unnamed: D10.1 (K), R10.1
unnamed: D10.2 (A), U10.15 (Q4)
unnamed: D11.1 (K), R11.1
unnamed: D11.2 (A), U9.14 (Q5)
unnamed: D12.1 (K), R12.1
unnamed: D12.2 (A), U10.14 (Q5)
unnamed: D13.1 (K), R13.1
unnamed: D13.2 (A), U9.13 (Q6)
unnamed: U1.9, U1.10, U1.11
unnamed: U2.11, U3.4 (E1)
unnamed: U7.2, U8.2 (Q0)
unnamed: U7.5, U8.5 (Q1)
unnamed: U7.10, U8.7 (Q2)
unnamed: U7.13, U8.10 (Q3)

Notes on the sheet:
08h-0Fh (SIO2)
38h-3Fh
GLUE LOGIC
00h-07h (SIO1)
BLINKENLIGHTS
BUS
18h-1Fh (CTC)
CPU & MEMORY
30h-37h
10h-17h (CF)
20h-27h (PIO1)
BANK SWITCHING
Bypass Capacitors
28h-2Fh

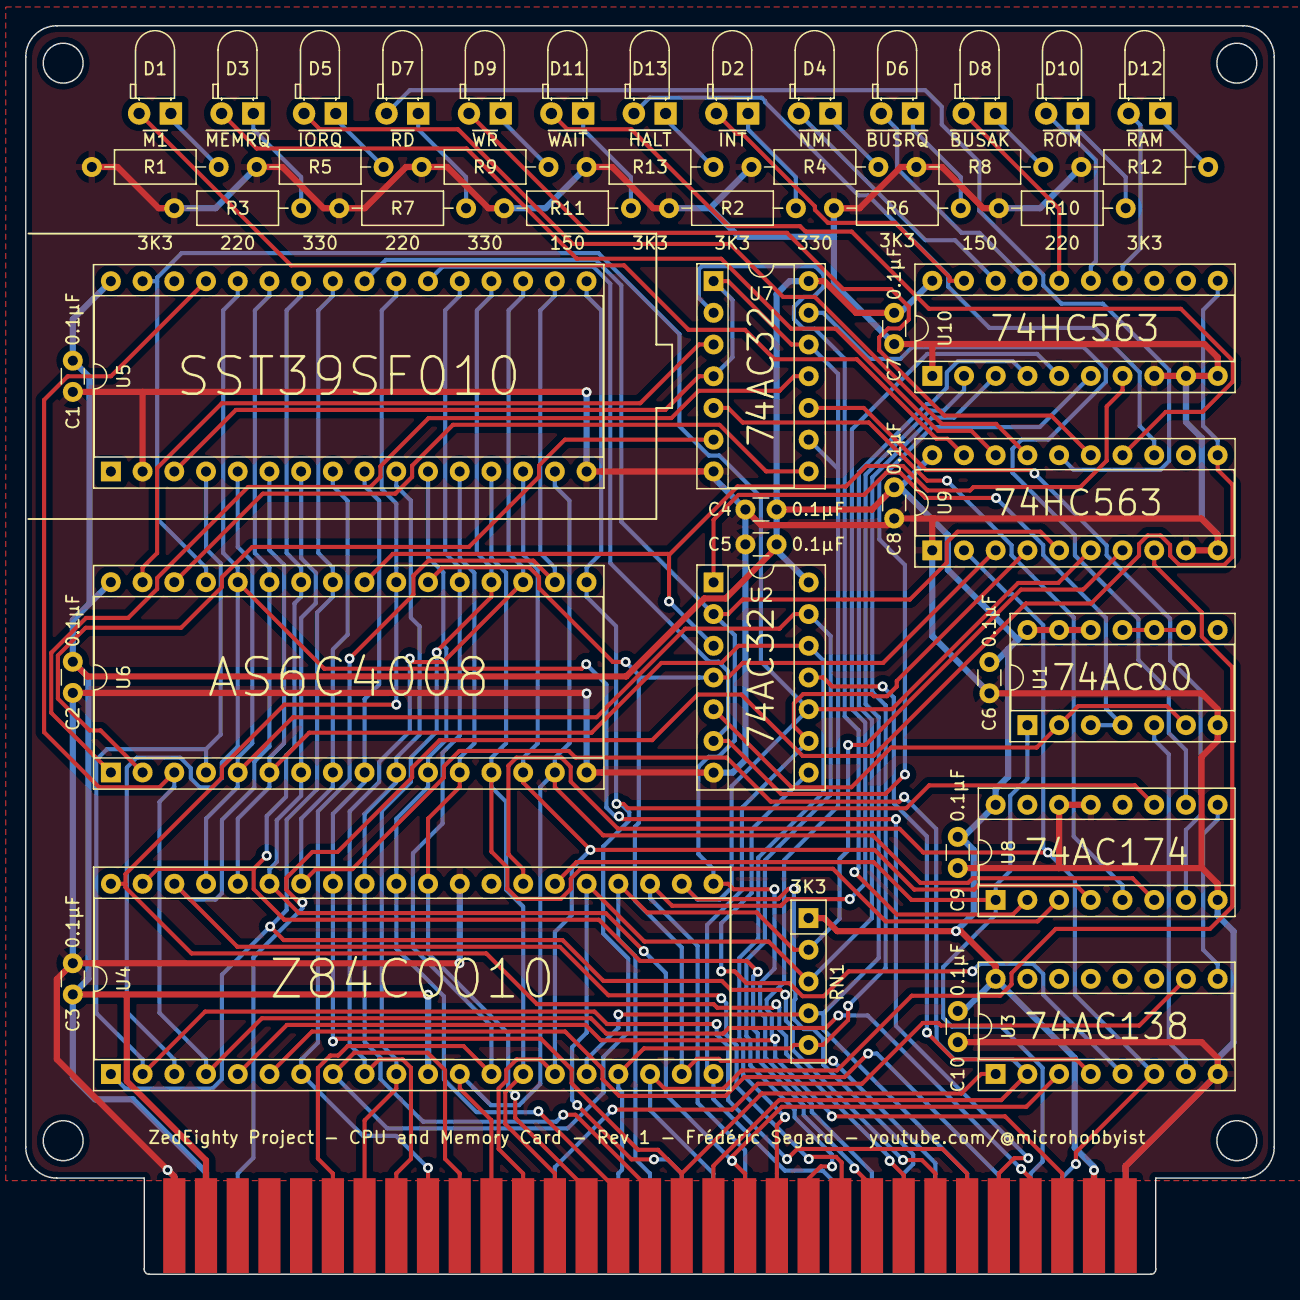
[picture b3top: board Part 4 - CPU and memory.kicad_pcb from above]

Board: 2 copper layers, 100.0 x 100.0 mm, 48 parts (0 on the bottom side), 84 nets.
